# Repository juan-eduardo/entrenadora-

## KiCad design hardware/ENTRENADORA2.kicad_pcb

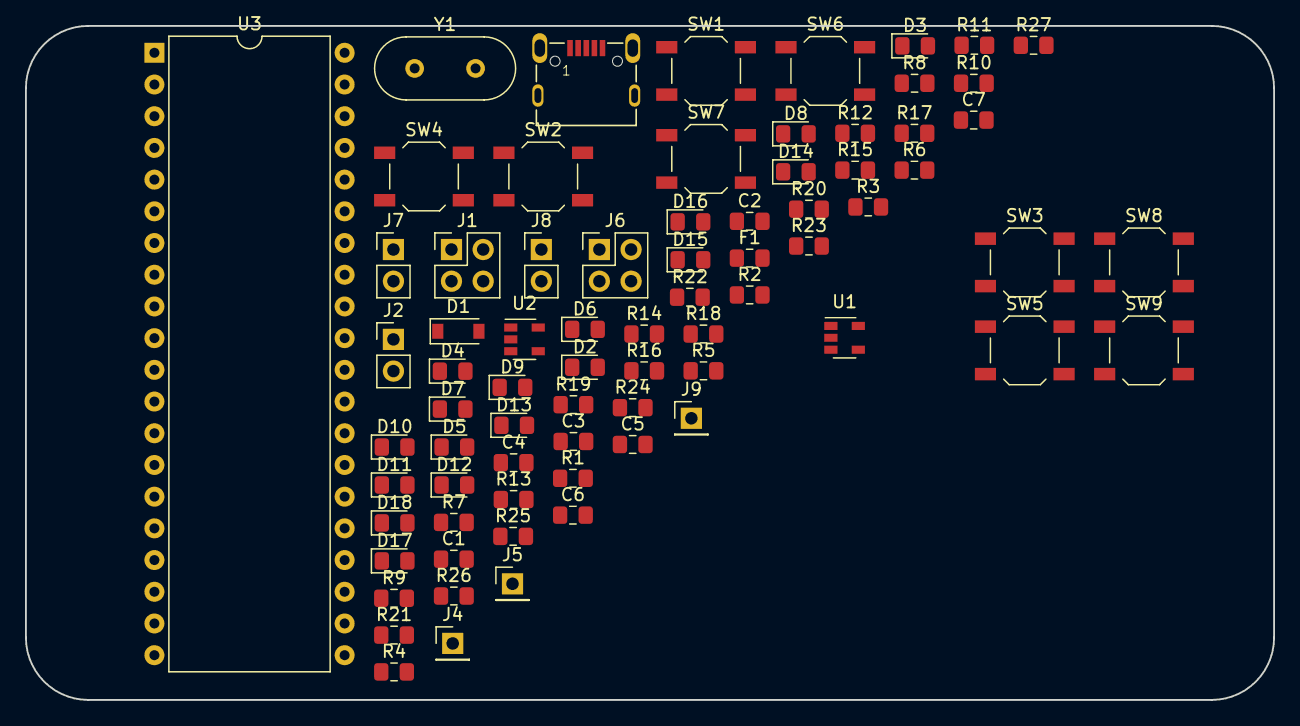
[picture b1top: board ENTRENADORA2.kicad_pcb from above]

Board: 2 copper layers, 100.0 x 54.0 mm, 75 parts (0 on the bottom side), 60 nets, no tracks yet.

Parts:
C1, C2, C3, C4, C5, C6, C7: C; C_0805_2012Metric_Pad1.15x1.40mm_HandSolder
D1: D_Schottky; D_SOD-123
D2, D3, D4, D5, D6, D7, D8, D9, D10, D11, D12, D13, D14, D15, D16, D17: LED_Small; LED_0805_2012Metric_Pad1.15x1.40mm_HandSolder
D18: LED; LED_0805_2012Metric_Pad1.15x1.40mm_HandSolder
F1: Polyfuse_Small; Fuse_0805_2012Metric_Pad1.15x1.40mm_HandSolder
J1, J6: PinHeader_2x02_P2.54mm_Vertical
J2, J7: Conn_01x02; PinHeader_1x02_P2.54mm_Vertical
J3: USB_B_Micro; 629105150521
J4, J5, J9: PinHeader_1x01_P2.54mm_Vertical
J8: PinHeader_1x02_P2.54mm_Vertical
R1, R2, R3, R4, R5, R6, R7, R8, R13, R14, R15, R16, R17, R18, R19, R20: R_Small; R_0805_2012Metric_Pad1.15x1.40mm_HandSolder
R9, R10, R11, R12, R21, R22, R23, R24, R25, R26, R27: R; R_0805_2012Metric_Pad1.15x1.40mm_HandSolder
SW1, SW2, SW3, SW4, SW5, SW6, SW7, SW8, SW9: SW_SPST_TL3342
U1: AP2112K-3.3TRG1; SOT-23-5
U2: MCP73831-2-OT; SOT-23-5
U3: PIC18F4550-IP; DIP-40_W15.24mm
Y1: Crystal; Crystal_HC49-U_Vertical

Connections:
+3V3: C2.1, J1.1, R27.1, U1.5, U3.11, U3.32
/+: J1.4, SW3.1, SW5.1, SW6.1, SW7.1
/-: J1.3, R9.1, R10.1, R11.1, R12.1, R21.1, R22.1, R23.1, R24.1
/B0: R12.2, U3.33
/B1: R11.2, SW3.2, U3.34
/B2: R10.2, U3.35
/B3: R9.2, SW5.2, U3.36
/B4: R23.2, SW6.2, U3.37
/B5: R21.2, SW7.2, U3.38
/B6: R22.2, U3.39
/B7: R24.2, U3.40
/BAT: C4.1, D1.2, J7.2, U2.3
/C0: D8.2, U3.15
/C1: D7.2, U3.16
/C2: D6.2, U3.17
/C3: D9.2, J9.1
/C4: D4.2, J5.1
/C5: D3.2, J4.1
/C6: D2.2, U3.25
/C7: D5.2, U3.26
/D0: D17.2, U3.19
/D1: D16.2, U3.20
/D2: D13.2, U3.21
/D3: D12.2, U3.22
/D4: D15.2, U3.27
/D5: D14.2, U3.28
/D6: D11.2, U3.29
/D7: D10.2, U3.30
/D+: J6.4, U3.24
/D-: J6.3, U3.23
/LEDS: J2.2, R1.1, R2.1, R3.1, R4.1, R5.1, R6.1, R7.1, R8.1, R13.1, R14.1, R15.1, R16.1, R17.1, R18.1, R19.1, R20.1
/O1: C6.2, U3.13, Y1.1
/O2: C7.2, U3.14, Y1.2
/RESET: R27.2, SW1.2, U3.1
/VUSB: J8.2, U3.18
GND: C1.2, C2.2, C3.2, C4.2, C5.2, C6.1, C7.1, J1.2, J2.1, J3.5, J7.1, R25.2, SW1.1, U1.2, U2.2, U3.12, U3.31
unnamed: C5.1, J8.1
unnamed: D2.1, R1.2
unnamed: D3.1, R2.2
unnamed: D4.1, R3.2
unnamed: D5.1, R4.2
unnamed: D6.1, R5.2
unnamed: D7.1, R6.2
unnamed: D8.1, R7.2
unnamed: D9.1, R8.2
unnamed: D10.1, R13.2
unnamed: D11.1, R14.2
unnamed: D12.1, R15.2
unnamed: D13.1, R16.2
unnamed: D14.1, R17.2
unnamed: D15.1, R18.2
unnamed: D16.1, R19.2
unnamed: D17.1, R20.2
unnamed: D18.1, U2.1
unnamed: D18.2, R26.1
unnamed: F1.2, J3.1
unnamed: J3.2, J6.2
unnamed: J3.3, J6.1
unnamed: R25.1, U2.5
VCC: C1.1, C3.1, D1.1, F1.1, R26.2, U1.1, U1.3, U2.4

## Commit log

2019-08-03 inicio
2019-08-03 librerias
